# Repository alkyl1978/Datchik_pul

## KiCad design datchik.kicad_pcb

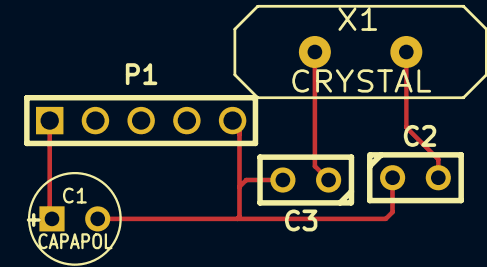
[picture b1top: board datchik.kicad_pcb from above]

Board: 2 copper layers, 5 parts (0 on the bottom side), 4 nets.

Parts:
C1: CAPAPOL; C1V5
C2, C3: C; C1
P1: CONN_5; PIN_ARRAY_5x1
X1: CRYSTAL; HC-18UV

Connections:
/VCC: C1.1, P1.1
/XTL1: C2.2, X1.2
/XTL2: C3.1, X1.1
GND: C1.2, C2.1, C3.2, P1.5

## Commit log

2014-10-30 init
2014-10-30 куьщеу
2014-10-30 добавлен разьем програмирования
2014-10-30 добавлена печатная плата
2014-10-30 добавлены файлы
2014-10-30 добавлен кварц и кондеры
2014-10-30 добавлены кондесаторы фильтра
2014-10-30 датчик пыли
